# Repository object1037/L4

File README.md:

# L4

The L4 is a 50% wireless split keyboard with an ortholinear layout.

- Keys: 52
- Switch: Choc V2 / MX
- Power: LiPo / CR2032
- Mount: Gasket / M2

## BOM

- Seeed XIAO BLE nRf52840 x 2
- Switch x 52
- Keycap x 52
- Diode(SOD123) x 52
- DP3T switch(SK23D07) x 2

### CR2032

- CR2032 battery x 4
- CR2032 holder(BC-2001) x 4
- Schottky diode(SOD123) x 4
- Capacitor(100uF, 3216) x 2
- PMOS(SSM3J332R) x 2

### LiPo

- LiPo battery x 2
- PH connector(side) x 2

### Acrylic case

- Case x 1
- M2 spacer
  - 1.6-2mm x 6
  - 3.5mm x 8
  - 6mm x 12
- M2 screw
  - 5mm x 10
  - 8mm x 6
  - 10mm x 8

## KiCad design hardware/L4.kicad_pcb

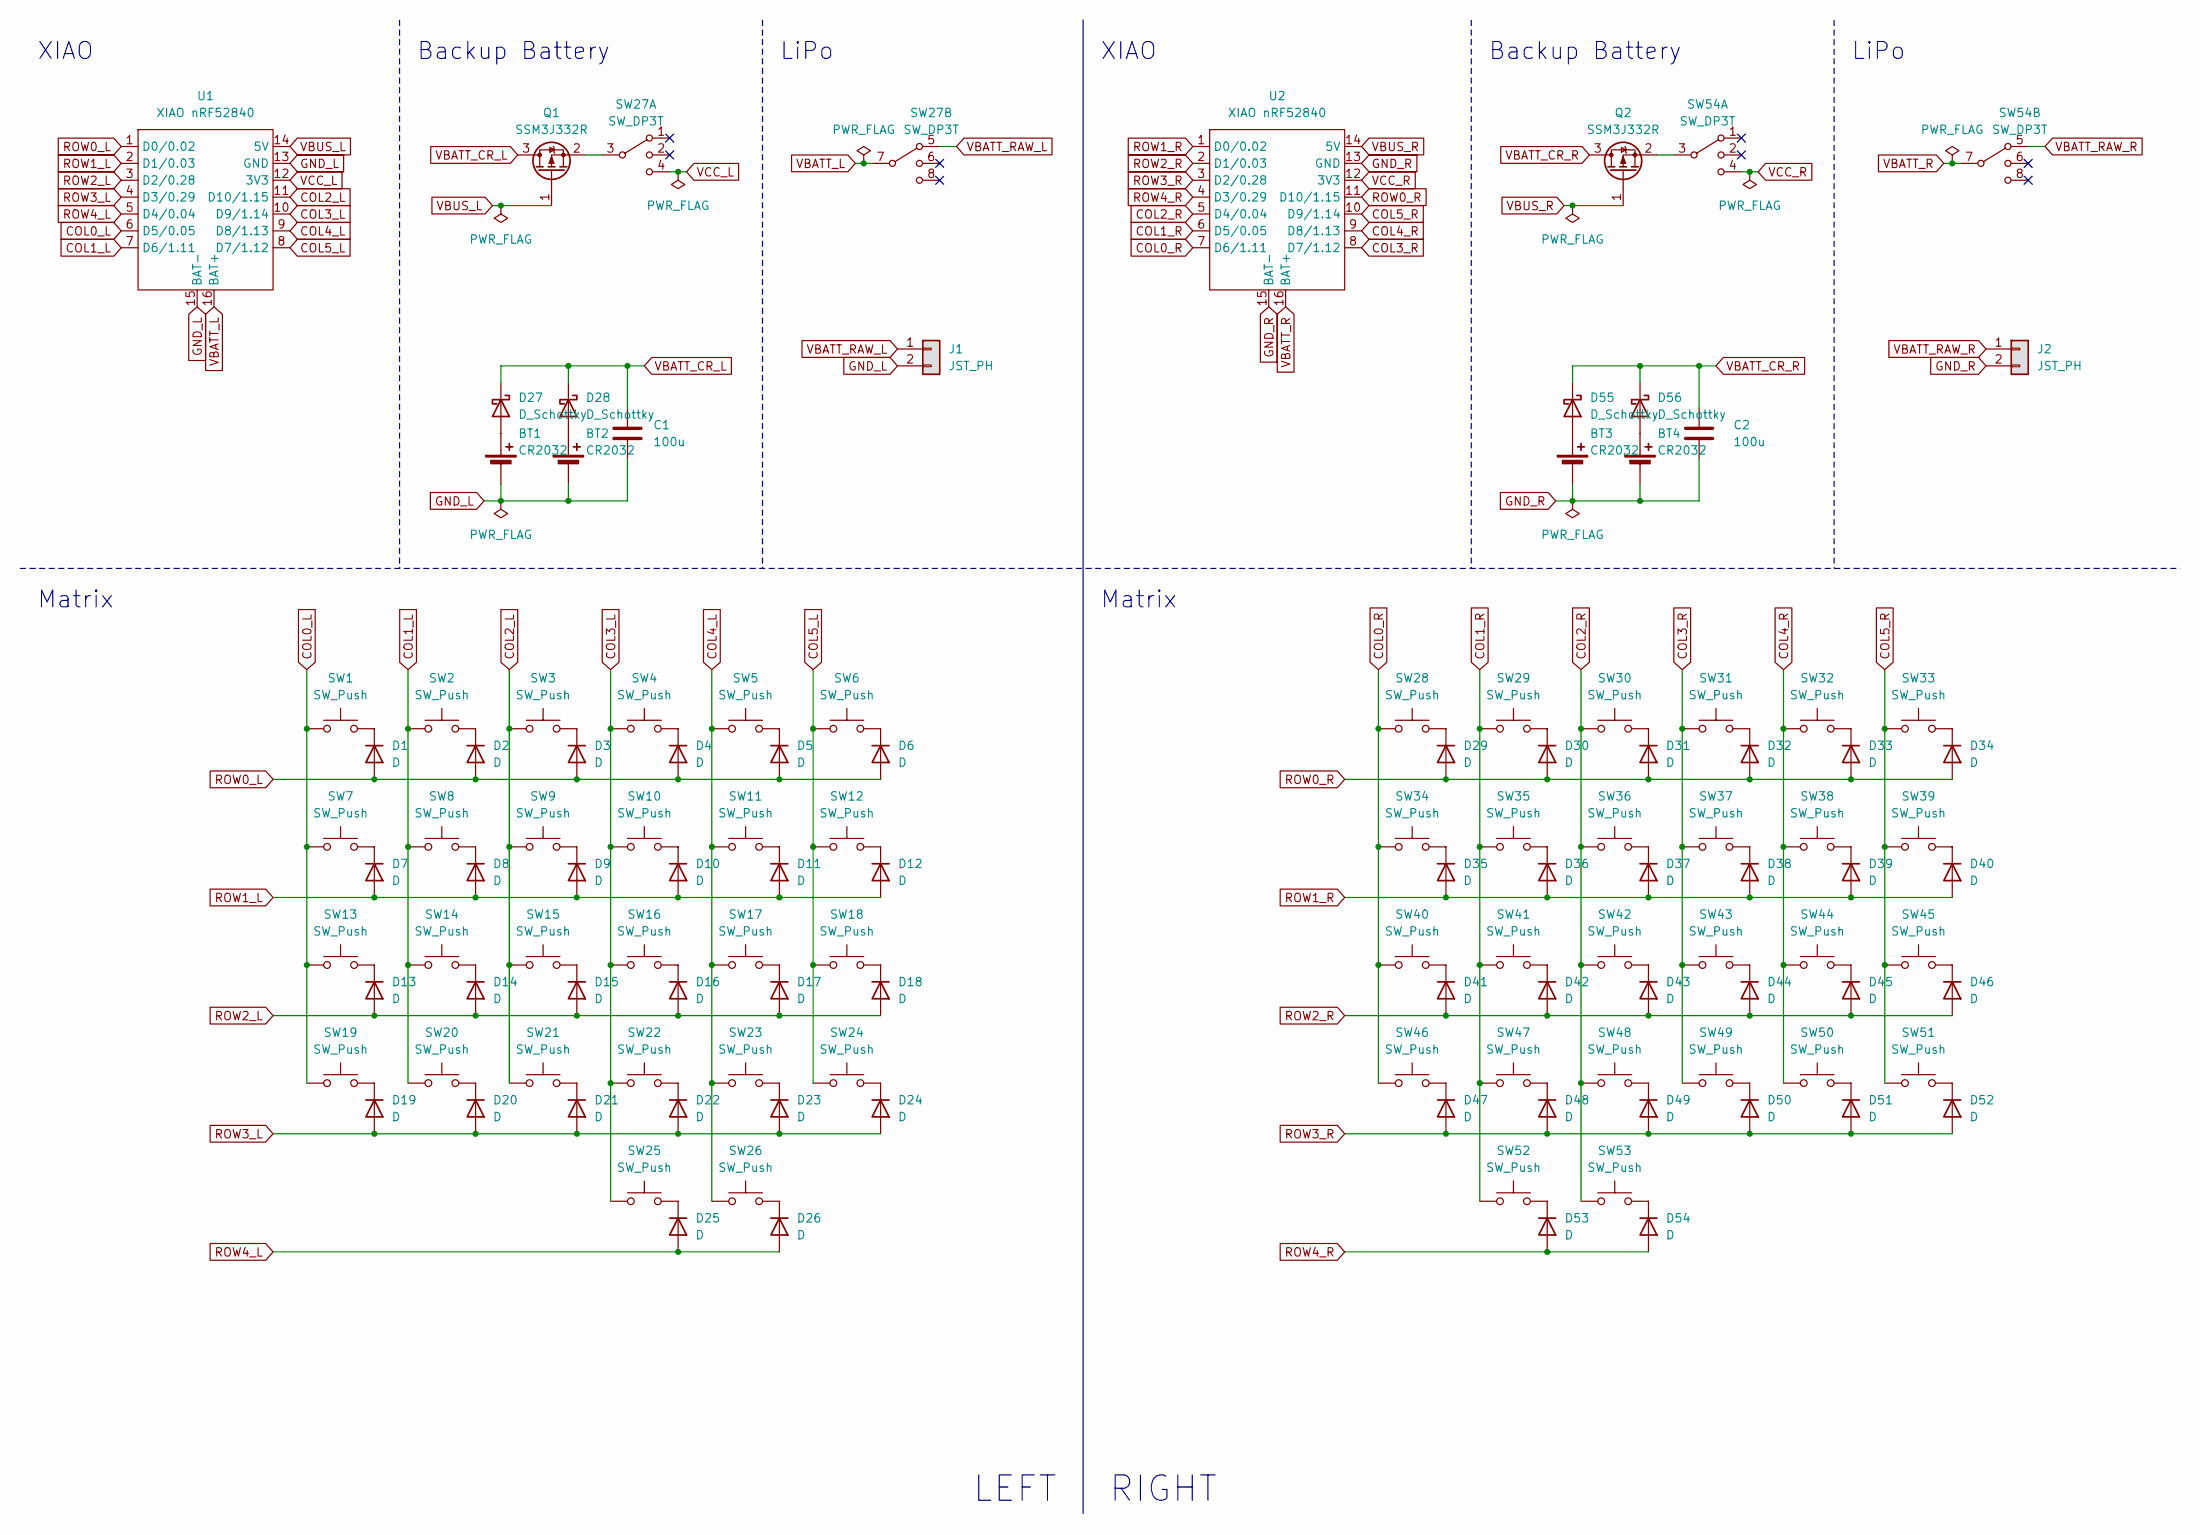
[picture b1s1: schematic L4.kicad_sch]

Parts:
BT1, BT2, BT3, BT4: CR2032; BatteryHolder_Multicomp_BC-2001_1x2032
C1, C2: 100u; C_1206_3216Metric_Pad1.33x1.80mm_HandSolder
D1, D2, D3, D4, D5, D6, D7, D8, D9, D10, D11, D12, D13, D14, D15, D16, D17, D18, D19, D20, D21, D22, D23, D24, D25, D26, D29, D30, D31, D32, D33, D34, D35, D36, D37, D38, D39, D40, D41, D42, D43, D44, D45, D46, D47, D48, D49, D50, D51, D52, D53, D54: D; D_SOD-123
D27, D28, D55, D56: D_Schottky; D_SOD-123
J1, J2: JST_PH; JST_PH_S2B-PH-K_1x02_P2.00mm_Horizontal
Q1, Q2: SSM3J332R; SOT-23-3
SW1, SW2, SW3, SW4, SW5, SW6, SW7, SW8, SW9, SW10, SW11, SW12, SW13, SW14, SW15, SW16, SW17, SW18, SW19, SW20, SW21, SW22, SW23, SW24, SW25, SW26, SW28, SW29, SW30, SW31, SW32, SW33, SW34, SW35, SW36, SW37, SW38, SW39, SW40, SW41, SW42, SW43, SW44, SW45, SW46, SW47, SW48, SW49, SW50, SW51, SW52, SW53: SW_Push; keyswitch_cherrymx_choc12_1u
SW27, SW54: SW_DP3T; SK23D07
U1, U2: XIAO nRF52840; XIAO_nrf52840

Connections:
COL0_L: SW1.1, SW7.1, SW13.1, SW19.1, U1.6 (D5/0.05)
COL0_R: SW28.1, SW34.1, SW40.1, SW46.1, U2.7 (D6/1.11)
COL1_L: SW2.1, SW8.1, SW14.1, SW20.1, U1.7 (D6/1.11)
COL1_R: SW29.1, SW35.1, SW41.1, SW47.1, SW52.1, U2.6 (D5/0.05)
COL2_L: SW3.1, SW9.1, SW15.1, SW21.1, U1.11 (D10/1.15)
COL2_R: SW30.1, SW36.1, SW42.1, SW48.1, SW53.1, U2.5 (D4/0.04)
COL3_L: SW4.1, SW10.1, SW16.1, SW22.1, SW25.1, U1.10 (D9/1.14)
COL3_R: SW31.1, SW37.1, SW43.1, SW49.1, U2.8 (D7/1.12)
COL4_L: SW5.1, SW11.1, SW17.1, SW23.1, SW26.1, U1.9 (D8/1.13)
COL4_R: SW32.1, SW38.1, SW44.1, SW50.1, U2.9 (D8/1.13)
COL5_L: SW6.1, SW12.1, SW18.1, SW24.1, U1.8 (D7/1.12)
COL5_R: SW33.1, SW39.1, SW45.1, SW51.1, U2.10 (D9/1.14)
GND_L: BT1.2 (-), BT2.2 (-), C1.2, J1.2, U1.13 (GND), U1.15 (BAT-)
GND_R: BT3.2 (-), BT4.2 (-), C2.2, J2.2, U2.13 (GND), U2.15 (BAT-)
unnamed: BT1.1 (+), D27.2 (A)
unnamed: BT2.1 (+), D28.2 (A)
unnamed: BT3.1 (+), D55.2 (A)
unnamed: BT4.1 (+), D56.2 (A)
unnamed: D1.1 (K), SW1.2
unnamed: D2.1 (K), SW2.2
unnamed: D3.1 (K), SW3.2
unnamed: D4.1 (K), SW4.2
unnamed: D5.1 (K), SW5.2
unnamed: D6.1 (K), SW6.2
unnamed: D7.1 (K), SW7.2
unnamed: D8.1 (K), SW8.2
unnamed: D9.1 (K), SW9.2
unnamed: D10.1 (K), SW10.2
unnamed: D11.1 (K), SW11.2
unnamed: D12.1 (K), SW12.2
unnamed: D13.1 (K), SW13.2
unnamed: D14.1 (K), SW14.2
unnamed: D15.1 (K), SW15.2
unnamed: D16.1 (K), SW16.2
unnamed: D17.1 (K), SW17.2
unnamed: D18.1 (K), SW18.2
unnamed: D19.1 (K), SW19.2
unnamed: D20.1 (K), SW20.2
unnamed: D21.1 (K), SW21.2
unnamed: D22.1 (K), SW22.2
unnamed: D23.1 (K), SW23.2
unnamed: D24.1 (K), SW24.2
unnamed: D25.1 (K), SW25.2
unnamed: D26.1 (K), SW26.2
unnamed: D29.1 (K), SW28.2
unnamed: D30.1 (K), SW29.2
unnamed: D31.1 (K), SW30.2
unnamed: D32.1 (K), SW31.2
unnamed: D33.1 (K), SW32.2
unnamed: D34.1 (K), SW33.2
unnamed: D35.1 (K), SW34.2
unnamed: D36.1 (K), SW35.2
unnamed: D37.1 (K), SW36.2
unnamed: D38.1 (K), SW37.2
unnamed: D39.1 (K), SW38.2
unnamed: D40.1 (K), SW39.2
unnamed: D41.1 (K), SW40.2
unnamed: D42.1 (K), SW41.2
unnamed: D43.1 (K), SW42.2
unnamed: D44.1 (K), SW43.2
unnamed: D45.1 (K), SW44.2
unnamed: D46.1 (K), SW45.2
unnamed: D47.1 (K), SW46.2
unnamed: D48.1 (K), SW47.2
unnamed: D49.1 (K), SW48.2
unnamed: D50.1 (K), SW49.2
unnamed: D51.1 (K), SW50.2
unnamed: D52.1 (K), SW51.2
unnamed: D53.1 (K), SW52.2
unnamed: D54.1 (K), SW53.2
unnamed: Q1.2 (S), SW27.3
unnamed: Q2.2 (S), SW54.3
ROW0_L: D1.2 (A), D2.2 (A), D3.2 (A), D4.2 (A), D5.2 (A), D6.2 (A), U1.1 (D0/0.02)
ROW0_R: D29.2 (A), D30.2 (A), D31.2 (A), D32.2 (A), D33.2 (A), D34.2 (A), U2.11 (D10/1.15)
ROW1_L: D7.2 (A), D8.2 (A), D9.2 (A), D10.2 (A), D11.2 (A), D12.2 (A), U1.2 (D1/0.03)
ROW1_R: D35.2 (A), D36.2 (A), D37.2 (A), D38.2 (A), D39.2 (A), D40.2 (A), U2.1 (D0/0.02)
ROW2_L: D13.2 (A), D14.2 (A), D15.2 (A), D16.2 (A), D17.2 (A), D18.2 (A), U1.3 (D2/0.28)
ROW2_R: D41.2 (A), D42.2 (A), D43.2 (A), D44.2 (A), D45.2 (A), D46.2 (A), U2.2 (D1/0.03)
ROW3_L: D19.2 (A), D20.2 (A), D21.2 (A), D22.2 (A), D23.2 (A), D24.2 (A), U1.4 (D3/0.29)
ROW3_R: D47.2 (A), D48.2 (A), D49.2 (A), D50.2 (A), D51.2 (A), D52.2 (A), U2.3 (D2/0.28)
ROW4_L: D25.2 (A), D26.2 (A), U1.5 (D4/0.04)
ROW4_R: D53.2 (A), D54.2 (A), U2.4 (D3/0.29)
VBATT_CR_L: C1.1, D27.1 (K), D28.1 (K), Q1.3 (D)
VBATT_CR_R: C2.1, D55.1 (K), D56.1 (K), Q2.3 (D)
VBATT_L: SW27.7, U1.16 (BAT+)
VBATT_R: SW54.7, U2.16 (BAT+)
VBATT_RAW_L: J1.1, SW27.5
VBATT_RAW_R: J2.1, SW54.5
VBUS_L: Q1.1 (G), U1.14 (5V)
VBUS_R: Q2.1 (G), U2.14 (5V)
VCC_L: SW27.4, U1.12 (3V3)
VCC_R: SW54.4, U2.12 (3V3)

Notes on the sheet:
XIAO
LiPo
RIGHT
Matrix
Backup Battery
LEFT

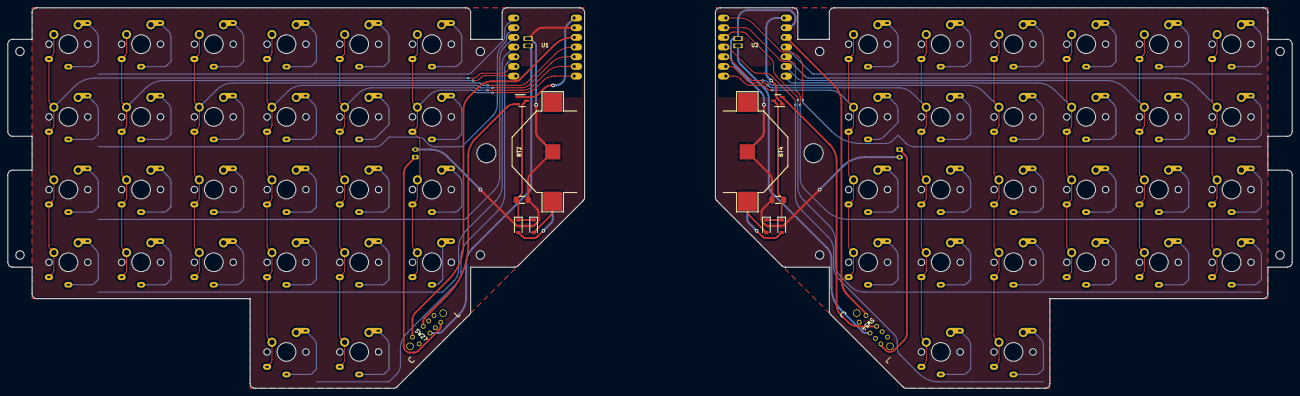
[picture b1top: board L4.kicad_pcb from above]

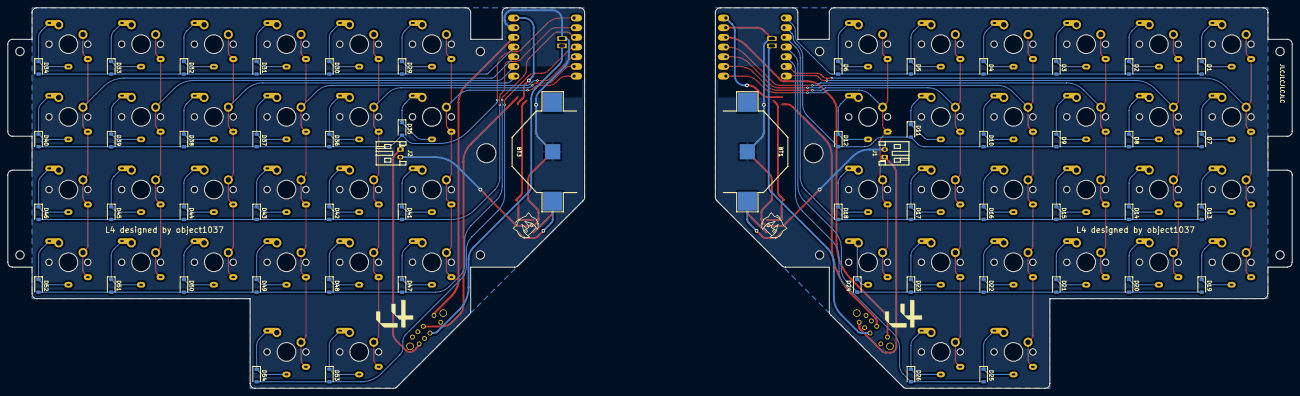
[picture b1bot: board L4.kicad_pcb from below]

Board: 2 copper layers, 336.5 x 99.7 mm, 122 parts (56 on the bottom side), 92 nets.

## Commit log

2024-05-04 init kicad project
2024-05-04 write left half schematic
2024-05-05 ignore unnecessary files
2024-05-05 finish right halve
2024-05-05 fix switch position
2024-05-05 link footprints
2024-05-06 finish part layout
2024-05-07 finish routing
2024-05-07 fillet left half
2024-05-08 apply fillets
2024-05-08 layout boards
2024-05-08 export step file
2024-05-08 update silks
2024-05-08 plot gerber
2024-05-08 rename
2024-05-09 fix edge cut
2024-05-09 output DXF files
2024-05-10 add upper cover
2024-05-10 add layout file
2024-05-10 arrange layout for A4 size
2024-05-14 add firmware as a submodule
2024-05-14 add README
2024-05-22 update firmware
2024-06-06 update submod
2024-06-28 add image
2025-10-26 update image url
2025-11-05 udate firmware
